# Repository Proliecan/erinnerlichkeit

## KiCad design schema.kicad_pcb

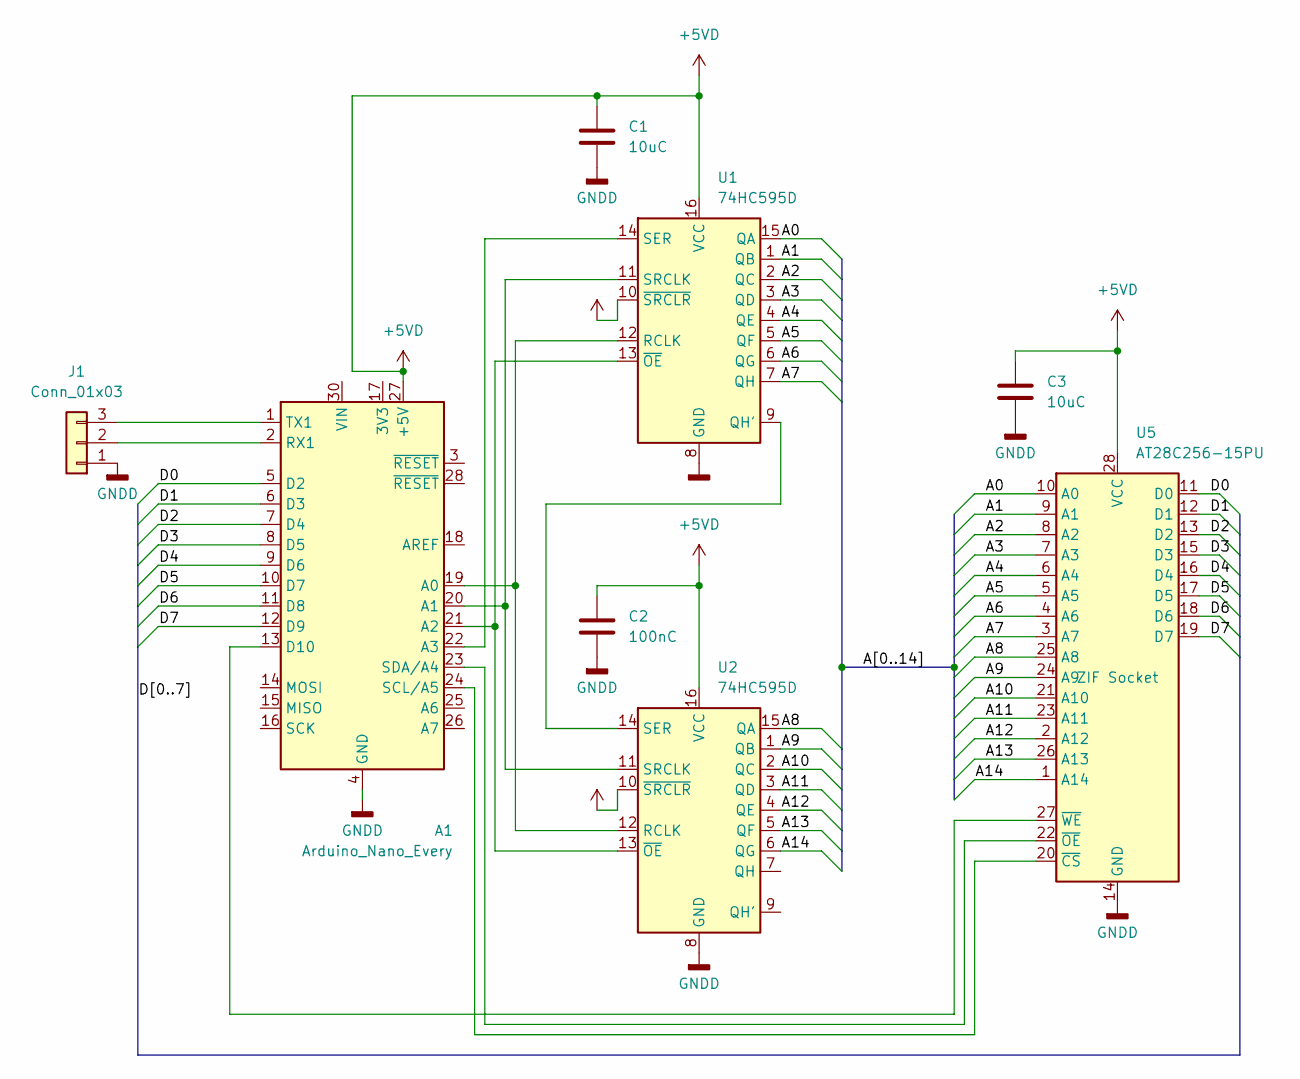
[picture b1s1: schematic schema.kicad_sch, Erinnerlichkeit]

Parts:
A1: Arduino_Nano_Every; Arduino_Nano
C1, C3: 10uC; C_0805_2012Metric_Pad1.18x1.45mm_HandSolder
C2: 100nC; C_0805_2012Metric_Pad1.18x1.45mm_HandSolder
J1: Conn_01x03; PinHeader_1x03_P2.54mm_Vertical
U1, U2: 74HC595D; SOIC-16_3.9x9.9mm_P1.27mm
U5: AT28C256-15PU; DIP_Socket-28_W11.9_W12.7_W15.24_W17.78_W18.5_3M_228-1277-0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

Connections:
+5VD: A1.27 (+5V), C1.1, C2.1, C3.1, U1.10 (~SRCLR), U1.16 (VCC), U2.10 (~SRCLR), U2.16 (VCC), U5.28 (VCC)
/A0: U1.15 (QA), U5.10 (A0)
/A1: U1.1 (QB), U5.9 (A1)
/A2: U1.2 (QC), U5.8 (A2)
/A3: U1.3 (QD), U5.7 (A3)
/A4: U1.4 (QE), U5.6 (A4)
/A5: U1.5 (QF), U5.5 (A5)
/A6: U1.6 (QG), U5.4 (A6)
/A7: U1.7 (QH), U5.3 (A7)
/A8: U2.15 (QA), U5.25 (A8)
/A9: U2.1 (QB), U5.24 (A9)
/A10: U2.2 (QC), U5.21 (A10)
/A11: U2.3 (QD), U5.23 (A11)
/A12: U2.4 (QE), U5.2 (A12)
/A13: U2.5 (QF), U5.26 (A13)
/A14: U2.6 (QG), U5.1 (A14)
/D0: A1.5 (D2), U5.11 (D0)
/D1: A1.6 (D3), U5.12 (D1)
/D2: A1.7 (D4), U5.13 (D2)
/D3: A1.8 (D5), U5.15 (D3)
/D4: A1.9 (D6), U5.16 (D4)
/D5: A1.10 (D7), U5.17 (D5)
/D6: A1.11 (D8), U5.18 (D6)
/D7: A1.12 (D9), U5.19 (D7)
GNDD: A1.4 (GND), A1.29 (GND), C1.2, C2.2, C3.2, J1.1, U1.8 (GND), U2.8 (GND), U5.14 (GND)
unnamed: A1.19 (A0), U1.12 (RCLK), U2.12 (RCLK)
unnamed: A1.20 (A1), U1.11 (SRCLK), U2.11 (SRCLK)
unnamed: A1.21 (A2), U1.13 (~OE), U2.13 (~OE)
unnamed: A1.22 (A3), U1.14 (SER)
unnamed: A1.13 (D10), U5.27 (~WE)
unnamed: A1.2 (RX1), J1.2
unnamed: A1.24 (SCL/A5), U5.20 (~CS)
unnamed: A1.23 (SDA/A4), U5.22 (~OE)
unnamed: A1.1 (TX1), J1.3
unnamed: U1.9 (QH'), U2.14 (SER)

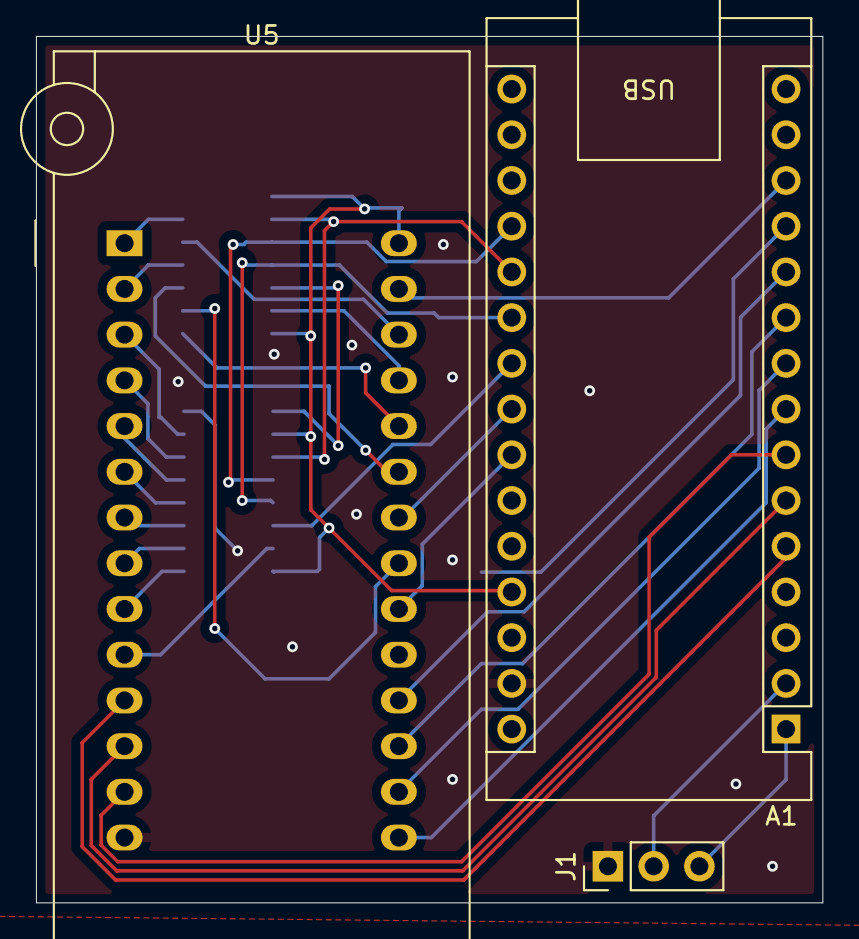
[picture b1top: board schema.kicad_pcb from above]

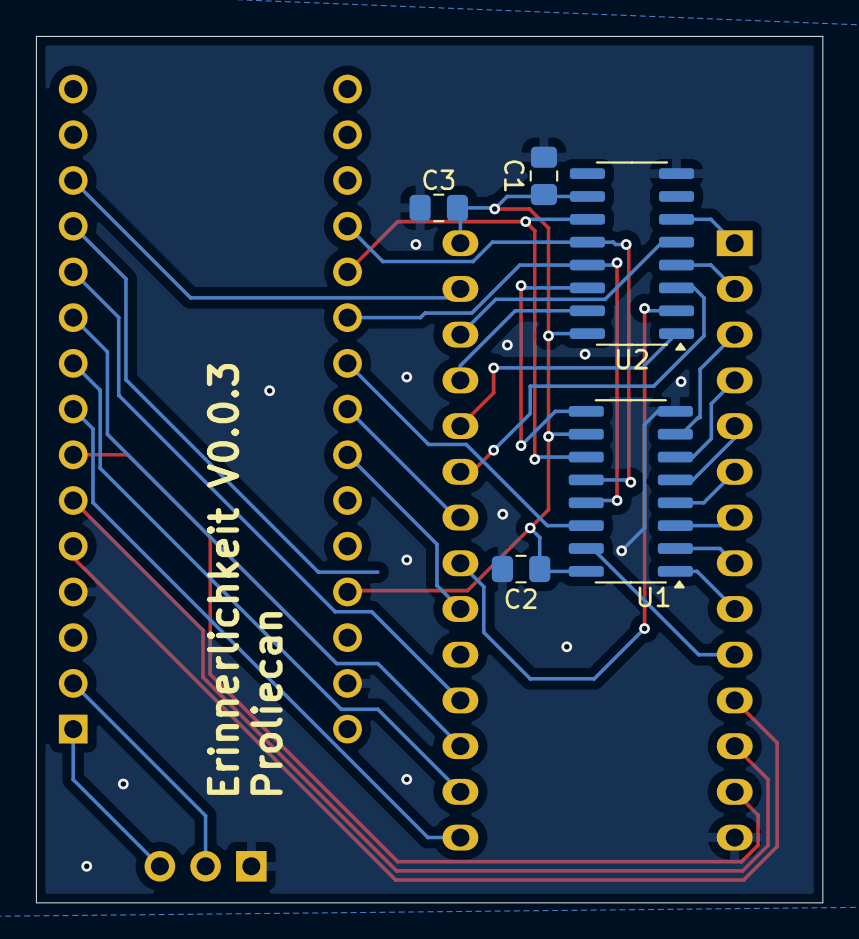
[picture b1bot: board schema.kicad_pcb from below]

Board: 2 copper layers, 43.7 x 48.1 mm, 8 parts (5 on the bottom side), 35 nets.

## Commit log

2024-05-02 fix-wrong-zif
2024-05-02 gitignore schema-backups
2024-05-03 Replace GNDD and +5VD wires with power symbols
2024-05-03 Remove lonely label
2024-05-03 Replace wires with busses
2024-05-03 Move bus labels
2024-05-03 Add condensators how I think is right
2024-05-03 small corrections
2024-05-03 Connect Control pins to MCU in schema
2024-05-03 Route traces (with warnings)
2024-05-03 Fix mistakes in ground plane
2024-05-03 ignore footprint errors
2024-05-03 fix flow
2024-05-03 update condensators
2024-05-03 update capacitor to 10uC
2024-05-04 ignore production files
2024-05-04 introduce jlcpcb toolkit
2024-05-04 reroute eeprom cs to arduino
2024-05-04 fix not enough digital pins
2024-05-04 change pinout
